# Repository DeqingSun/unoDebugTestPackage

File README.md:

# Arduino Board Package to Debug Uno/ATmega328P with CH552 debugger in Arduino IDE 2.0.0

**This repo is prepared for students in the Prototyping Electronic Devices class**

## Hardware for debugging

There are 3 hardware options:

### Using CH552 breakout board and ATmega328P on Breadboard

### Using CH552 breakout board and Arduino Uno board

There is a 100nF auto-reset capacitor on the serial adapter side of the jumper. And that capacitor will absorb the high frequency debug signal. So we need to cut the jumper for debugging. The jumper can be connected with a drop of solder after debugging to restore the auto-reset feature. 

### Using All in One board

### CH552 pinout and ATmega328P connection

| CH552 	| ATmega328P 	| Functionality 	|
|-------	|------------	|---------------	|
| P11   	| RST        	| ISP/DEBUG     	|
| P15   	| D11 (MOSI) 	| ISP           	|
| P16   	| D12 (MISO) 	| ISP           	|
| P17   	| D13 (SCK)  	| ISP           	|
| P30   	| D1 (TX)    	| Serial        	|
| P31   	| D0 (RX)    	| Serial        	|
| 5V    	| 5V         	| Power         	|
| GND   	| GND        	| Power         	|

## Software for debugging

### Install driver for Windows user

The debugger does not need any driver for Mac OS. But it does need LibUSB driver for the debugging/programming interface on Windows. Using [Zadig](zadig.akeo.ie) to install the libusb-win32 driver. 

### Burn the bootloader to reset Arduino firmware and fuse

Select **Arduino Uno** from the **Tools->Board** menu, and **USBtinyISP** as the **Tools->Programmer**

Then select **Burn Bootloader**.

If you are able to burn the bootloader, it means the hardware set is ready to be debugged. Your Arduino is also ready to be used as a regular Arduino Uno. 

Note if the Arduino has been debugged before burning the bootloader, your first burn attempt will fail, but the debugger will kick the Arduino out of debugging mode. Your second attempt will be successful. Also replug your board afterward, because Arduino can not enter debug mode again in the same power cycle that you unprogram the DWEN fuse.

### Add board support

In Arduino **Preferences**, Click button on the right of the **Additional Boards Manager URLs**

Add:

https://raw.githubusercontent.com/DeqingSun/unoDebugTestPackage/main/package_uno_debug_index.json

Open **Boards Manager** from **Tools**->**Boards: "Whatever"**->**Boards Manager**

In the **Boards Manager**, Find **Arduino 8-bit with Debug**. Install it.

### Start Debugging

Open BlinkUno.ino with Arduino IDE 2.0.0.

Click **Select Board**, if your board is already plugged in, you should be able to set the board and port automatically.

Or you can manually set the board and port.

Click **Verify** icon then click the **Start debugging** icon.

Your board should be able to enter debug mode and pause on start.

If you encounter an error. Try to replug the board and debug again.

If it still does not work, try to:

1. Replug the board.
2. Try to burn the bootloader again. (try 2nd time if debugged before).
3. Replug the board.
4. Try to debug again. 

Then you should be able to debug the code.

### Update Code in Debugging

When you modify the Arduino code and want to update the code within the Arduino chip, you can stop debugging, click **Verify** icon then click the **Start debugging** icon. The debugger will automatically send the new compiled binary to the Arduino chip through the debugging interface.

Note you can not use the regular upload button in Debugging mode, because the bootloader is disabled. 

### Quit Debugging and restore bootloader

When you finish debugging, first stop debugging. Then burn the bootloader twice and the board will quit debugging mode and restore the regular Arduino Uno bootloader. 

The first bootloader burn will fail for sure, but the debugging probe (CH552) will send a quit signal to ATmega328P and enable the ISP interface, then the second bootloader burn will be successful. A power cycle is recommended after the successful burn if you want to debug again later.

## Acknowledgment

The DebugWire protocol investigation and documentation by [RikusW](http://www.ruemohr.org/docs/debugwire.html). The DebugWire protocol is the foundation to debug the ATmega328P.

[dwire-debug](https://github.com/dcwbrown/dwire-debug) project from David C W Brown. The dwire-debug acts as debugger server for avr-gdb. The dwire-debug binary in this repo was compiled with this [branch](https://github.com/DeqingSun/dwire-debug/tree/ArduinoProIDEAlphaTest) with some hack mentioned in the [Arduino IDE issue](https://github.com/arduino/arduino-ide/issues/87#issuecomment-775660437). The DigiSpark/ATTiny85 firmware in dwire-debug project also helped a lot in developing the CH552 firmware.

USBTINY PID/VID usage permission from Limor Fried for class teaching usage. The PID/VID usage create seamless experience with existing bootloader burning feature in the Arduino IDE. 

Pre-compiled avr-gdb from [Microchip website](https://www.microchip.com/en-us/tools-resources/develop/microchip-studio/gcc-compilers).

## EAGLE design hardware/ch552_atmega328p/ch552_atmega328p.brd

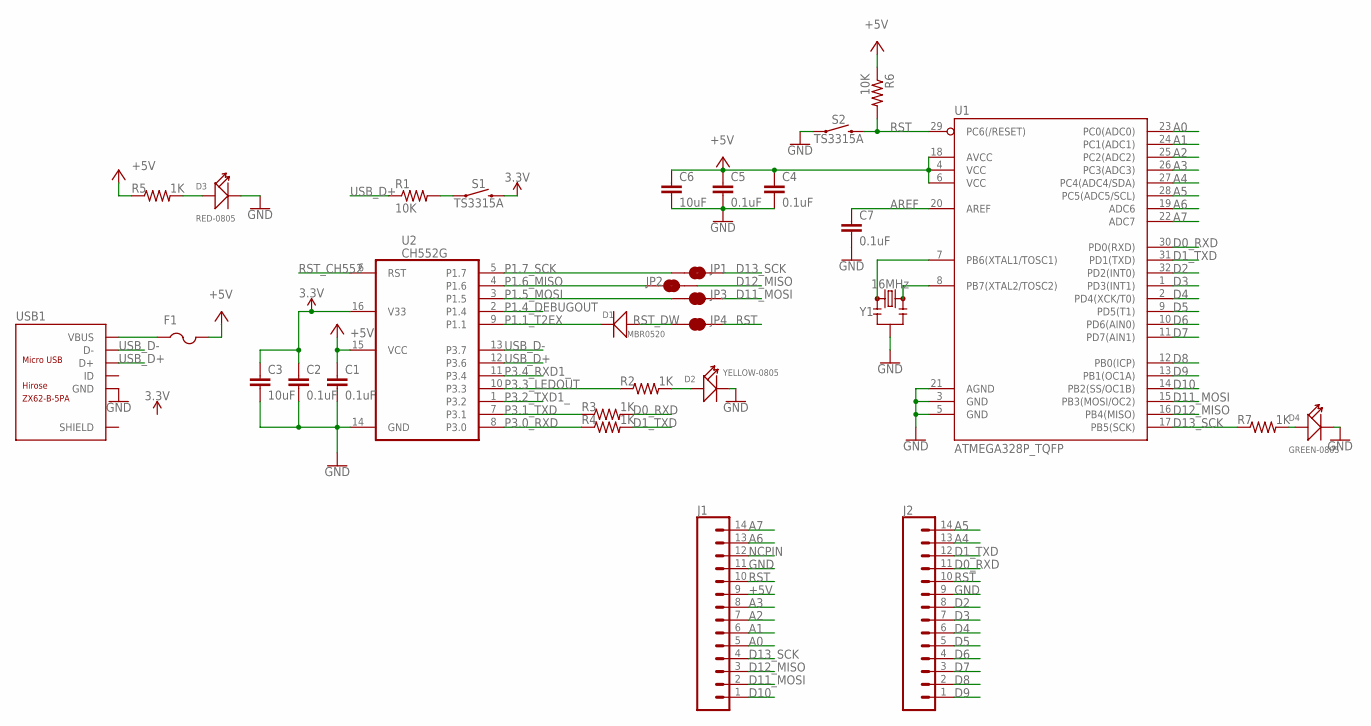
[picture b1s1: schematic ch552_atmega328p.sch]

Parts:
C1, C2, C4, C5, C7: 0.1uF; C0805K; LCSC C16834
C3, C6: 10uF; C0805K; LCSC C307525
D1: MBR0520; SOD-123
D2: YELLOW-0805; LED-0805
D3: RED-0805; LED-0805
D4: GREEN-0805; LED-0805
F1: PTCFUSE-1206; R1206; LCSC C151162
J1, J2: CONN_14NO_SILK; 1X14_NO_SILK
JP1, JP2, JP3, JP4: JUMPER-SMT_2_NC_TRACE_NO-SILK; SMT-JUMPER_2_NC_TRACE_NO-SILK
R1, R6: 10K; R0805
R2, R3, R4, R5, R7: 1K; R0805
S1, S2: TS3315A; TACTILE_SWITCH_SMD_3.3MM; LCSC C412367
U1: ATMEGA328P_TQFP; TQFP32-08
U2: CH552G; MY_IC_SO16; LCSC C111292
USB1: ZX62-B-5PA; MICRO-USB5+6P-SMD-0.65-AB; LCSC C10418
Y1: 16MHz; RESONATOR-SMD-3.2X1.3

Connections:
3.3V: C2.1, C3.1, S1.3 (2), U2.16 (V33)
+5V: C1.1, C4.1, C5.1, C6.1, F1.2, J1.9, R5.1, R6.1, U1.4 (VCC), U1.6 (VCC), U1.18 (AVCC), U2.15 (VCC)
A0: J1.5, U1.23 (PC0(ADC0))
A1: J1.6, U1.24 (PC1(ADC1))
A2: J1.7, U1.25 (PC2(ADC2))
A3: J1.8, U1.26 (PC3(ADC3))
A4: J2.13, U1.27 (PC4(ADC4/SDA))
A5: J2.14, U1.28 (PC5(ADC5/SCL))
A6: J1.13, U1.19 (ADC6)
A7: J1.14, U1.22 (ADC7)
AREF: C7.1, U1.20 (AREF)
D0_RXD: J2.11, R3.2, U1.30 (PD0(RXD))
D1_TXD: J2.12, R4.2, U1.31 (PD1(TXD))
D2: J2.8, U1.32 (PD2(INT0))
D3: J2.7, U1.1 (PD3(INT1))
D4: J2.6, U1.2 (PD4(XCK/T0))
D5: J2.5, U1.9 (PD5(T1))
D6: J2.4, U1.10 (PD6(AIN0))
D7: J2.3, U1.11 (PD7(AIN1))
D8: J2.2, U1.12 (PB0(ICP))
D9: J2.1, U1.13 (PB1(OC1A))
D10: J1.1, U1.14 (PB2(SS/OC1B))
D11_MOSI: J1.2, JP3.2, U1.15 (PB3(MOSI/OC2))
D12_MISO: J1.3, JP2.2, U1.16 (PB4(MISO))
D13_SCK: J1.4, JP1.2, R7.1, U1.17 (PB5(SCK))
GND: C1.2, C2.2, C3.2, C4.2, C5.2, C6.2, C7.2, D2.-, D3.-, D4.-, J1.11, J2.9, S2.1, U1.3 (GND), U1.5 (GND), U1.21 (AGND), U2.14 (GND), USB1.5 (GND), Y1.2
unnamed: R1.2, S1.1
unnamed: D2.+, R2.2
unnamed: D3.+, R5.2
unnamed: D4.+, R7.2
unnamed: U1.8 (PB7(XTAL2/TOSC2)), Y1.3
unnamed: U1.7 (PB6(XTAL1/TOSC1)), Y1.1
NCPIN: J1.12
P1.1_T2EX: D1.-, U2.9 (P1.1)
P1.4_DEBUGOUT: U2.2 (P1.4)
P1.5_MOSI: JP3.1, U2.3 (P1.5)
P1.6_MISO: JP2.1, U2.4 (P1.6)
P1.7_SCK: JP1.1, U2.5 (P1.7)
P3.0_RXD: R4.1, U2.8 (P3.0)
P3.1_TXD: R3.1, U2.7 (P3.1)
P3.2_TXD1_: U2.1 (P3.2)
P3.3_LEDOUT: R2.1, U2.10 (P3.3)
P3.4_RXD1_: U2.11 (P3.4)
RST: J1.10, J2.10, JP4.2, R6.2, S2.3 (2), U1.29 (PC6(/RESET))
RST_CH552: U2.6 (RST)
RST_DW: D1.+, JP4.1
USB_D+: R1.1, U2.12 (P3.6), USB1.3 (D+)
USB_D-: U2.13 (P3.7), USB1.2 (D-)
VBUS: F1.1, USB1.1 (VBUS)

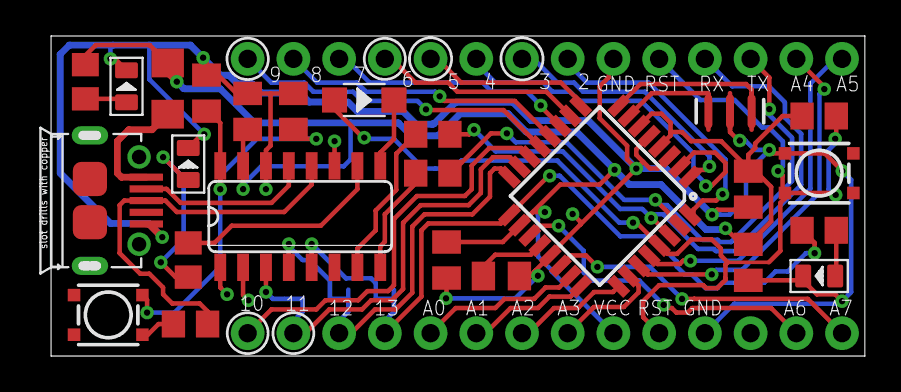
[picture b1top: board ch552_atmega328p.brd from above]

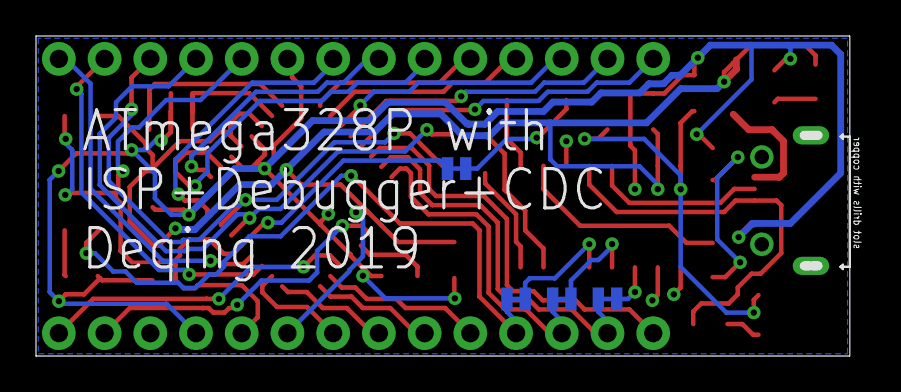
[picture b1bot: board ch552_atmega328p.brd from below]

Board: 2 copper layers, 45.5 x 17.3 mm, 31 parts (4 on the bottom side), 44 nets.

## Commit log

2020-10-13 add files can compile
2020-10-13 add tools
2020-10-14 update debug tool and receipt
2020-12-19 update code
2021-03-27 update 0.0.3
    enable dwen
2022-10-16 add tool for windows
2022-10-17 add packscript
2022-10-17 update path
2022-10-18 Add boards file and images
2022-11-05 update avr-gdb to 3.7.0
    This prevents the python2.7 not found problem in Monterey. Binary from https://www.microchip.com/en-us/tools-resources/develop/microchip-studio/gcc-compilers
2022-11-05 update json
2023-09-08 update new version
2023-09-10 add type A connector option
2024-10-18 Add optimized version of tinyspi firmware, 16M OK
2025-08-31 try update avr version
2025-08-31 update checksum
2025-08-31 update from zip to tar

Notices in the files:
parts and their libraries:
SparkFun-IC-Microcontroller: Licensing: Creative Commons ShareAlike 4.0 International - https://creativecommons.org/licenses/by-sa/4.0
